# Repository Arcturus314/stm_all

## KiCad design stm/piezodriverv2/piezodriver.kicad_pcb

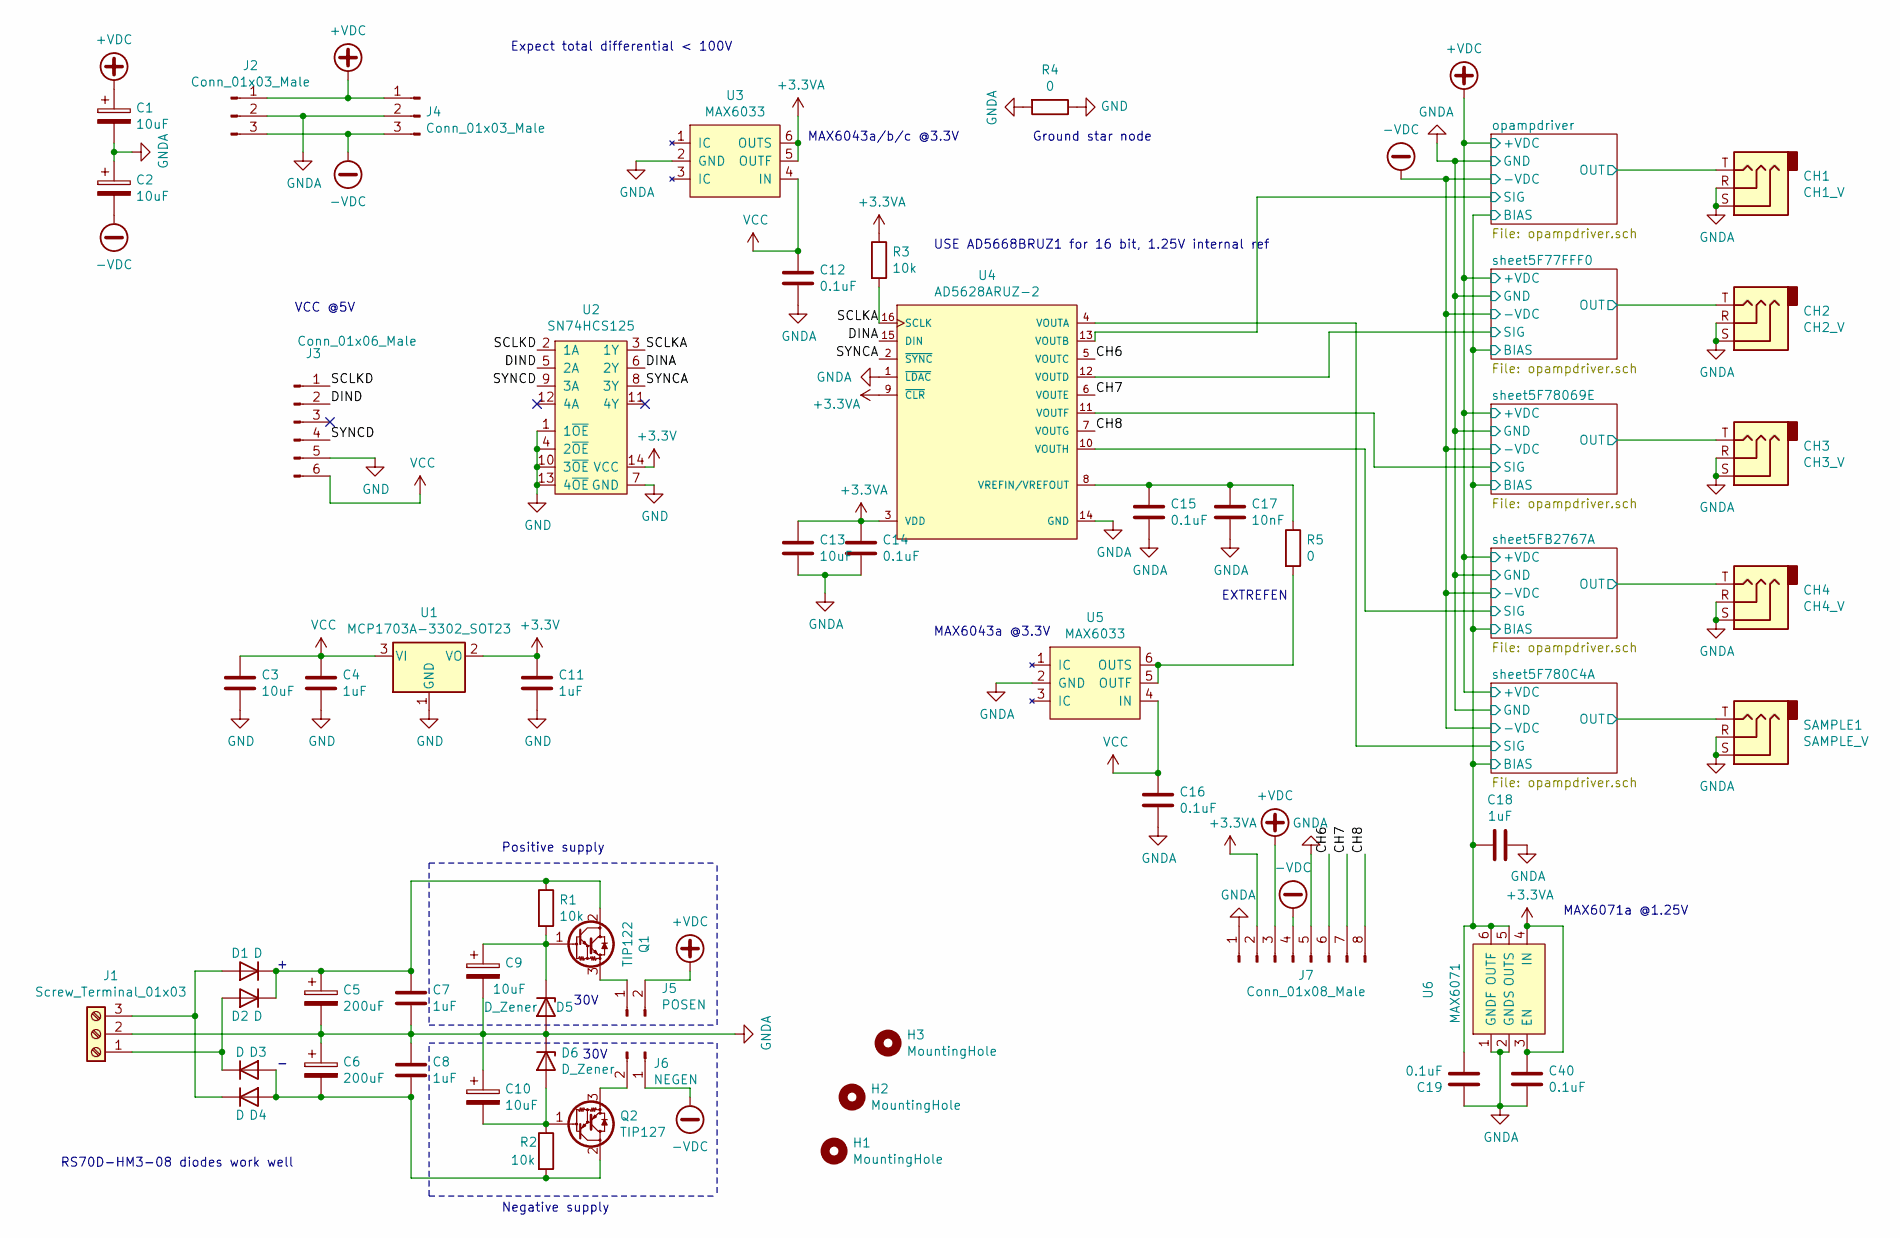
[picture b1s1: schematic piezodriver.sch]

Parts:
C1, C2, C9, C10: 10uF; CP_Radial_D5.0mm_P2.50mm
C3, C13: 10uF; C_0805_2012Metric_Pad1.18x1.45mm_HandSolder
C4, C7, C8, C11, C18: 1uF; C_0805_2012Metric_Pad1.18x1.45mm_HandSolder
C5, C6: 200uF; CP_Radial_D12.5mm_P5.00mm
C12, C14, C15, C16, C19, C40: 0.1uF; C_0805_2012Metric_Pad1.18x1.45mm_HandSolder
C17: 10nF; C_0805_2012Metric_Pad1.18x1.45mm_HandSolder
CH1: CH1_V; Jack_3.5mm_CUI_SJ-3523-SMT_Horizontal
CH2: CH2_V; Jack_3.5mm_CUI_SJ-3523-SMT_Horizontal
CH3: CH3_V; Jack_3.5mm_CUI_SJ-3523-SMT_Horizontal
CH4: CH4_V; Jack_3.5mm_CUI_SJ-3523-SMT_Horizontal
D1, D2, D3, D4: D; D_SMF
D5, D6: D_Zener; D_SOD-323_HandSoldering
H1, H2, H3: MountingHole; MountingHole_3.2mm_M3
J1: Screw_Terminal_01x03; TerminalBlock_Phoenix_MKDS-1,5-3-5.08_1x03_P5.08mm_Horizont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
J2, J4: Conn_01x03_Male; PinHeader_1x03_P2.54mm_Vertical
J3: Conn_01x06_Male; PinHeader_1x06_P2.54mm_Vertical
J5: POSEN; PinHeader_1x02_P2.54mm_Vertical
J6: NEGEN; PinHeader_1x02_P2.54mm_Vertical
J7: Conn_01x08_Male; PinHeader_1x08_P2.54mm_Vertical
Q1: TIP122; TO-220-3_Vertical
Q2: TIP127; TO-220-3_Vertical
R1, R2, R3: 10k; R_0805_2012Metric_Pad1.20x1.40mm_HandSolder
R4, R5: 0; R_0805_2012Metric_Pad1.20x1.40mm_HandSolder
SAMPLE1: SAMPLE_V; Jack_3.5mm_CUI_SJ-3523-SMT_Horizontal
U1: MCP1703A-3302_SOT23; SOT-23
U2: SN74HCS125; TSSOP-14_4.4x5mm_P0.65mm
U3, U5: MAX6033; SOT-23-6_Handsoldering
U4: AD5628ARUZ-2; TSSOP-16_4.4x5mm_P0.65mm
U6: MAX6071; SOT-23-6_Handsoldering

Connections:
+3.3VA: C13.1, C14.1, C40.1, J7.2, R3.1, U3.5 (OUTF), U3.6 (OUTS), U4.3 (VDD), U4.9 (~CLR~), U6.3 (EN), U6.4 (IN)
+3V3: C11.1, U1.2 (VO), U2.14 (VCC)
+VDC: C1.1, J2.1, J4.1, J5.2, J7.3; also elsewhere on the board
-VDC: C2.2, J2.3, J4.3, J6.1, J7.4; also elsewhere on the board
/CH6: J7.6, U4.5 (VOUTC)
/CH7: J7.7, U4.6 (VOUTE)
/CH8: J7.8, U4.7 (VOUTG)
/DINA: U2.6 (2Y), U4.15 (DIN)
/DIND: J3.2, U2.5 (2A)
/SCLKA: R3.2, U2.3 (1Y), U4.16 (SCLK)
/SCLKD: J3.1, U2.2 (1A)
/SYNCA: U2.8 (3Y), U4.2 (~SYNC~)
/SYNCD: J3.4, U2.9 (3A)
/opampdriver/BIAS: C18.1, C19.2, U6.5 (OUTS), U6.6 (OUTF); also elsewhere on the board
/opampdriver/OUT: CH1.T; also elsewhere on the board
/opampdriver/SIG: U4.13 (VOUTB); also elsewhere on the board
/sheet5F77FFF0/OUT: CH2.T; also elsewhere on the board
/sheet5F77FFF0/SIG: U4.12 (VOUTD); also elsewhere on the board
/sheet5F780C4A/OUT: SAMPLE1.T; also elsewhere on the board
/sheet5F780C4A/SIG: U4.4 (VOUTA); also elsewhere on the board
/sheet5F78069E/OUT: CH3.T; also elsewhere on the board
/sheet5F78069E/SIG: U4.11 (VOUTF); also elsewhere on the board
/sheet5FB2767A/OUT: CH4.T; also elsewhere on the board
/sheet5FB2767A/SIG: U4.10 (VOUTH); also elsewhere on the board
GND: C3.2, C4.2, C11.2, J3.5, R4.1, U1.1 (GND), U2.1 (1~OE), U2.4 (2~OE), U2.7 (GND), U2.10 (3~OE), U2.13 (4~OE)
GNDA: C1.2, C2.1, C5.2, C6.1, C7.2, C8.1, C9.2, C10.1, C12.2, C13.2, C14.2, C15.2, C16.2, C17.2, C18.2, C19.1, C40.2, CH1.R, CH1.S, CH2.R, CH2.S, CH3.R, CH3.S, CH4.R, CH4.S, D5.2 (A), D6.1 (K), J1.2, J2.2, J4.2, J7.1, J7.5, R4.2, SAMPLE1.R, SAMPLE1.S, U3.2 (GND), U4.1 (~LDAC~), U4.14 (GND), U5.2 (GND), U6.1 (GNDF), U6.2 (GNDS); also elsewhere on the board
unnamed: C5.1, C7.1, D1.1 (K), D2.1 (K), Q1.2 (C), R1.1
unnamed: C6.2, C8.2, D3.2 (A), D4.2 (A), Q2.2 (C), R2.2
unnamed: C9.1, D5.1 (K), Q1.1 (B), R1.2
unnamed: C10.2, D6.2 (A), Q2.1 (B), R2.1
unnamed: C15.1, C17.1, R5.1, U4.8 (VREFIN/VREFOUT)
unnamed: D1.2 (A), D4.1 (K), J1.3
unnamed: D2.2 (A), D3.1 (K), J1.1
unnamed: J5.1, Q1.3 (E)
unnamed: J6.2, Q2.3 (E)
unnamed: R5.2, U5.5 (OUTF), U5.6 (OUTS)
VCC: C3.1, C4.1, C12.1, C16.1, J3.6, U1.3 (VI), U3.4 (IN), U5.4 (IN)

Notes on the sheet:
Expect total differential < 100V
USE AD5668BRUZ1 for 16 bit, 1.25V internal ref
EXTREFEN
MAX6043a @3.3V
MAX6071a @1.25V
VCC @5V
Ground star node
MAX6043a/b/c @3.3V
RS70D-HM3-08 diodes work well
Negative supply
30V
Positive supply

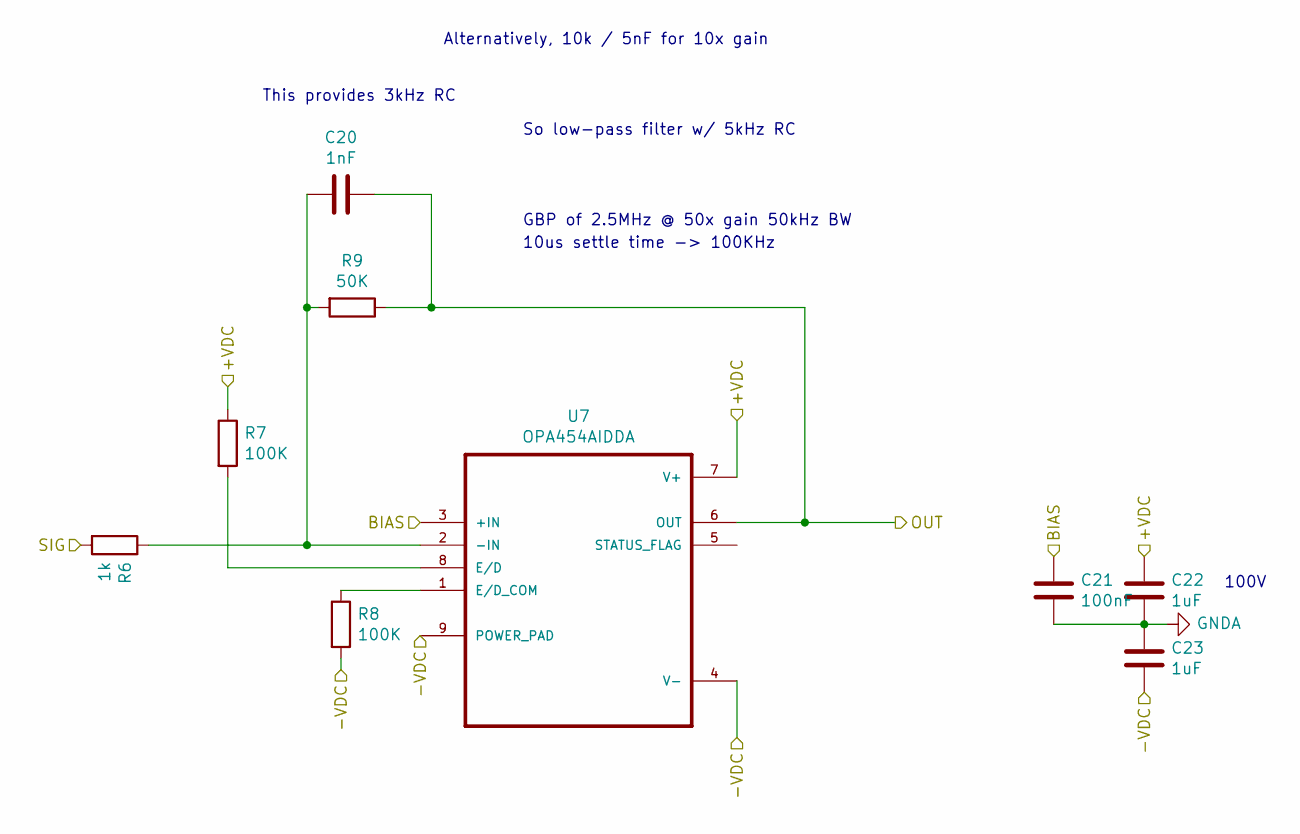
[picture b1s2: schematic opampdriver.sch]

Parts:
C20: 1nF; C_0805_2012Metric_Pad1.18x1.45mm_HandSolder
C21: 100nF; C_0805_2012Metric_Pad1.18x1.45mm_HandSolder
C22, C23: 1uF; C_0805_2012Metric_Pad1.18x1.45mm_HandSolder
R6: 1k; R_0805_2012Metric_Pad1.20x1.40mm_HandSolder
R7, R8: 100K; R_0805_2012Metric_Pad1.20x1.40mm_HandSolder
R9: 50K; R_0805_2012Metric_Pad1.20x1.40mm_HandSolder
U7: OPA454AIDDA; NOPB

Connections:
+VDC: C22.1, R7.1, U7.7 (V+); also elsewhere on the board
-VDC: C23.2, R8.2, U7.4 (V-), U7.9 (POWER_PAD); also elsewhere on the board
/opampdriver/BIAS: C21.1, U7.3 (+IN); also elsewhere on the board
/opampdriver/OUT: C20.1, R9.1, U7.6 (OUT); also elsewhere on the board
/opampdriver/SIG: R6.2; also elsewhere on the board
GNDA: C21.2, C22.2, C23.1; also elsewhere on the board
unnamed: C20.2, R6.1, R9.2, U7.2 (-IN)
unnamed: R7.2, U7.8 (E/D)
unnamed: R8.1, U7.1 (E/D_COM)

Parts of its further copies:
C24, C28, C32, C36: 1nF; C_0805_2012Metric_Pad1.18x1.45mm_HandSolder
C25, C29, C33, C37: 100nF; C_0805_2012Metric_Pad1.18x1.45mm_HandSolder
C26, C27, C30, C31, C34, C35, C38, C39: 1uF; C_0805_2012Metric_Pad1.18x1.45mm_HandSolder
R10, R14, R18, R22: 1k; R_0805_2012Metric_Pad1.20x1.40mm_HandSolder
R11, R12, R15, R16, R19, R20, R23, R24: 100K; R_0805_2012Metric_Pad1.20x1.40mm_HandSolder
R13, R17, R21, R25: 50K; R_0805_2012Metric_Pad1.20x1.40mm_HandSolder
U8, U9, U10, U11: OPA454AIDDA; NOPB

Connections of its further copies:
+VDC: C26.1, C30.1, C34.1, C38.1, R11.1, R15.1, R19.1, R23.1, U8.7 (V+), U9.7 (V+), U10.7 (V+), U11.7 (V+); also elsewhere on the board
-VDC: C27.2, C31.2, C35.2, C39.2, R12.2, R16.2, R20.2, R24.2, U8.4 (V-), U8.9 (POWER_PAD), U9.4 (V-), U9.9 (POWER_PAD), U10.4 (V-), U10.9 (POWER_PAD), U11.4 (V-), U11.9 (POWER_PAD); also elsewhere on the board
/opampdriver/BIAS: C25.1, C29.1, C33.1, C37.1, U8.3 (+IN), U9.3 (+IN), U10.3 (+IN), U11.3 (+IN); also elsewhere on the board
/sheet5F77FFF0/OUT: C24.1, R13.1, U8.6 (OUT); also elsewhere on the board
/sheet5F77FFF0/SIG: R10.2; also elsewhere on the board
/sheet5F780C4A/OUT: C32.1, R21.1, U10.6 (OUT); also elsewhere on the board
/sheet5F780C4A/SIG: R18.2; also elsewhere on the board
/sheet5F78069E/OUT: C28.1, R17.1, U9.6 (OUT); also elsewhere on the board
/sheet5F78069E/SIG: R14.2; also elsewhere on the board
/sheet5FB2767A/OUT: C36.1, R25.1, U11.6 (OUT); also elsewhere on the board
/sheet5FB2767A/SIG: R22.2; also elsewhere on the board
GNDA: C25.2, C26.2, C27.1, C29.2, C30.2, C31.1, C33.2, C34.2, C35.1, C37.2, C38.2, C39.1; also elsewhere on the board
unnamed: C24.2, R10.1, R13.2, U8.2 (-IN)
unnamed: C28.2, R14.1, R17.2, U9.2 (-IN)
unnamed: C32.2, R18.1, R21.2, U10.2 (-IN)
unnamed: C36.2, R22.1, R25.2, U11.2 (-IN)
unnamed: R11.2, U8.8 (E/D)
unnamed: R12.1, U8.1 (E/D_COM)
unnamed: R15.2, U9.8 (E/D)
unnamed: R16.1, U9.1 (E/D_COM)
unnamed: R19.2, U10.8 (E/D)
unnamed: R20.1, U10.1 (E/D_COM)
unnamed: R23.2, U11.8 (E/D)
unnamed: R24.1, U11.1 (E/D_COM)

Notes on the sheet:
GBP of 2.5MHz @ 50x gain 50kHz BW
10us settle time -> 100KHz
So low-pass filter w/ 5kHz RC
This provides 3kHz RC
Alternatively, 10k / 5nF for 10x gain
100V

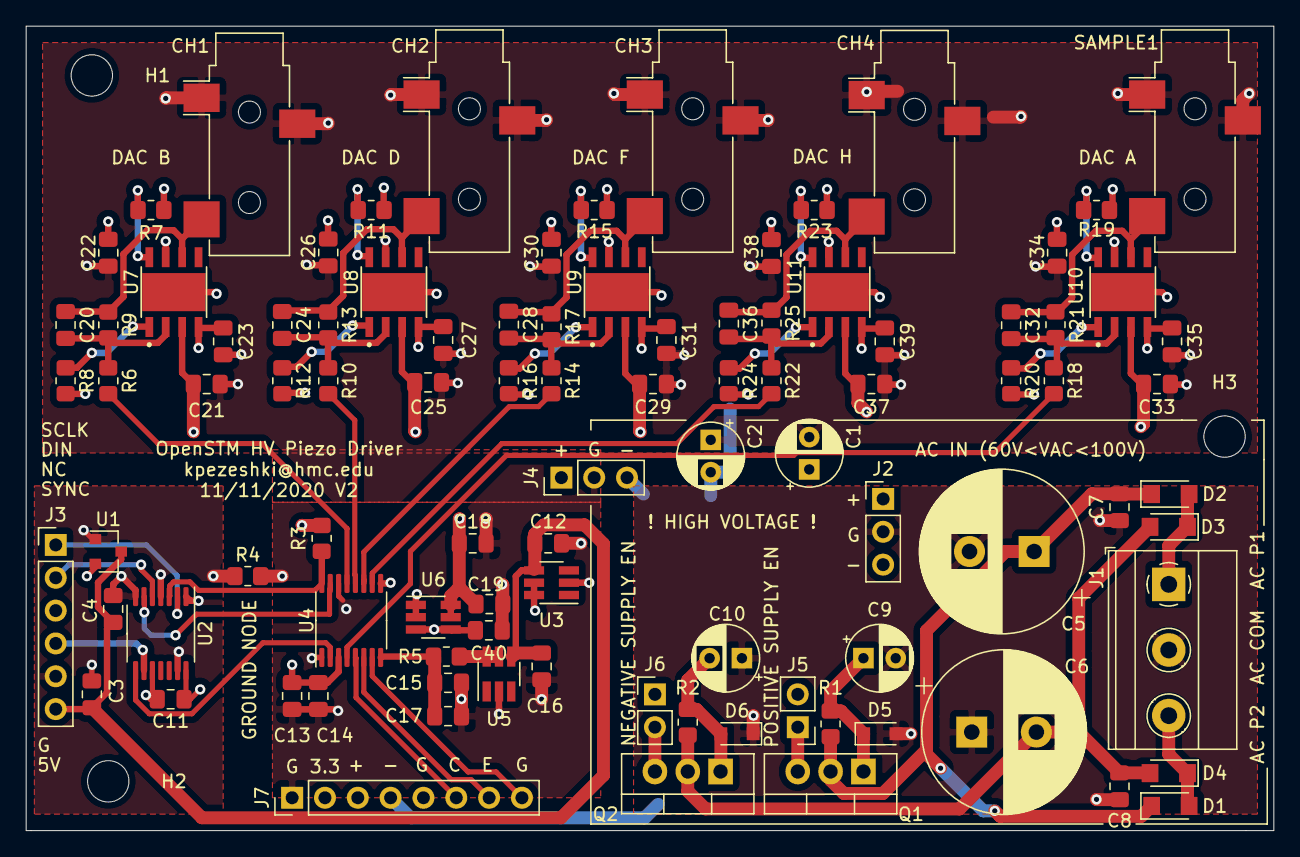
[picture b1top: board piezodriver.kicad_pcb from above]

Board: 4 copper layers, 96.5 x 62.2 mm, 99 parts (0 on the bottom side), 52 nets.

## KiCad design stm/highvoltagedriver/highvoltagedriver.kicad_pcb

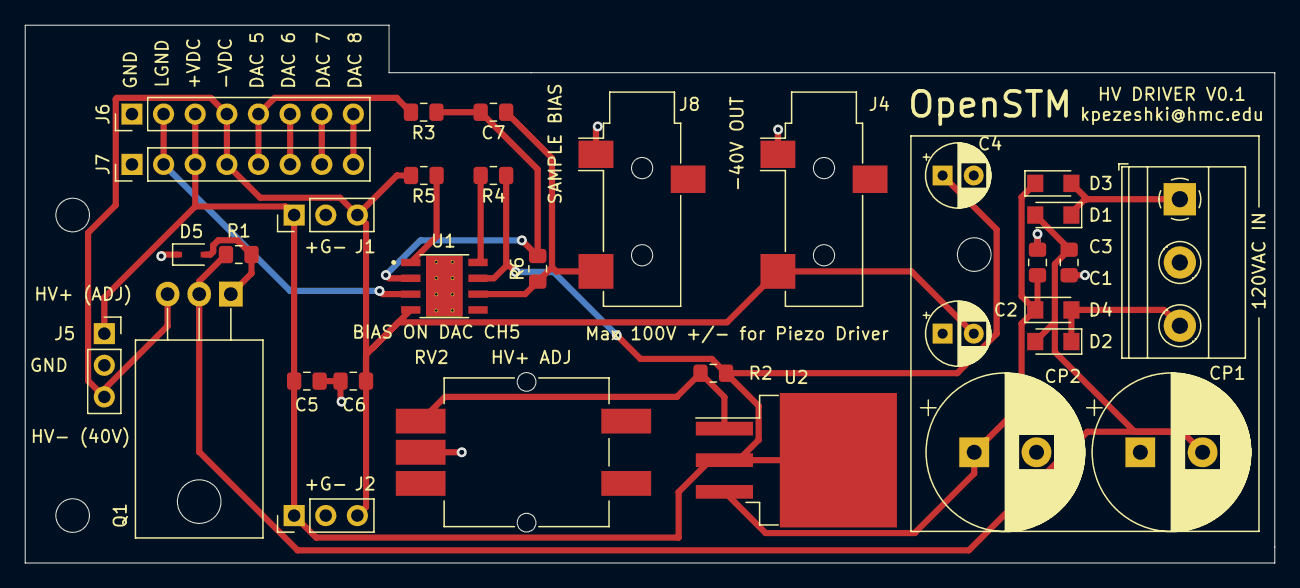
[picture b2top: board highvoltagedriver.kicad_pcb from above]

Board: 2 copper layers, 100.3 x 43.2 mm, 32 parts (0 on the bottom side), 18 nets.

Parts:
C1, C3, C5, C6: 1uF; C_0805_2012Metric_Pad1.15x1.40mm_HandSolder
C2, C4: 10uF; CP_Radial_D5.0mm_P2.50mm
C7: 1nF; C_0805_2012Metric_Pad1.15x1.40mm_HandSolder
CP1, CP2: 200uF; CP_Radial_D12.5mm_P5.00mm
D1, D2, D3, D4: D; D_SMF
D5: D_Zener; D_SOD-323
J1, J2: Conn_01x03_Male; PinHeader_1x03_P2.54mm_Vertical
J3: Screw_Terminal_01x03; TerminalBlock_Phoenix_MKDS-1,5-3-5.08_1x03_P5.08mm_Horizont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
J4, J8: AudioJack2; Jack_3.5mm_CUI_SJ-3523-SMT_Horizontal
J5: Conn_01x03_Female; PinSocket_1x03_P2.54mm_Vertical
J6: Conn_01x08_Male; PinHeader_1x08_P2.54mm_Vertical
J7: Conn_01x08_Female; PinHeader_1x08_P2.54mm_Vertical
Q1: TIP127; TO-220-3_Horizontal_TabDown
R1: 10k; R_0805_2012Metric_Pad1.15x1.40mm_HandSolder
R2: 100; R_0805_2012Metric_Pad1.15x1.40mm_HandSolder
R3: 1k; R_0805_2012Metric_Pad1.15x1.40mm_HandSolder
R4, R5: 100K; R_0805_2012Metric_Pad1.15x1.40mm_HandSolder
R6: 50K; R_0805_2012Metric_Pad1.15x1.40mm_HandSolder
RV2: 10k; Potentiometer_Bourns_PRS11S_Vertical
U1: OPA454AIDDA; NOPB
U2: TL783; TO-263-3_TabPin2

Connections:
/DACBIAS: J6.5, J7.5, R3.2
/HVN: C2.2, C6.1, J1.3, J2.3, J4.T, J5.3, J6.4, J7.4, Q1.3, R5.2, U1.4
/HVP: C4.1, C5.1, J1.1, J2.1, J5.1, J6.3, J7.3, R2.2, R4.1, U1.7, U2.2
/biasamp/BIAS: J6.2, J7.2, U1.3
/biasamp/OUT: C7.1, J8.T, R6.1, U1.6
/hvpower/negreg/VNEG: C1.2, CP1.2, D1.2, D2.2, Q1.2, R1.2
GND: C1.1, C2.1, C3.2, C4.2, C5.2, C6.2, CP1.1, CP2.2, D5.1, J1.2, J2.2, J3.2, J4.S, J5.2, J6.1, J7.1, J8.S, RV2.2
unnamed: C3.1, CP2.1, D3.1, D4.1, U2.3
unnamed: C7.2, R3.1, R6.2, U1.2
unnamed: D1.1, D3.2, J3.1
unnamed: D2.1, D4.2, J3.3
unnamed: D5.2, Q1.1, R1.1
unnamed: J6.6, J7.6
unnamed: J6.7, J7.7
unnamed: J6.8, J7.8
unnamed: R2.1, RV2.1, U2.1
unnamed: R4.2, U1.8
unnamed: R5.1, U1.1

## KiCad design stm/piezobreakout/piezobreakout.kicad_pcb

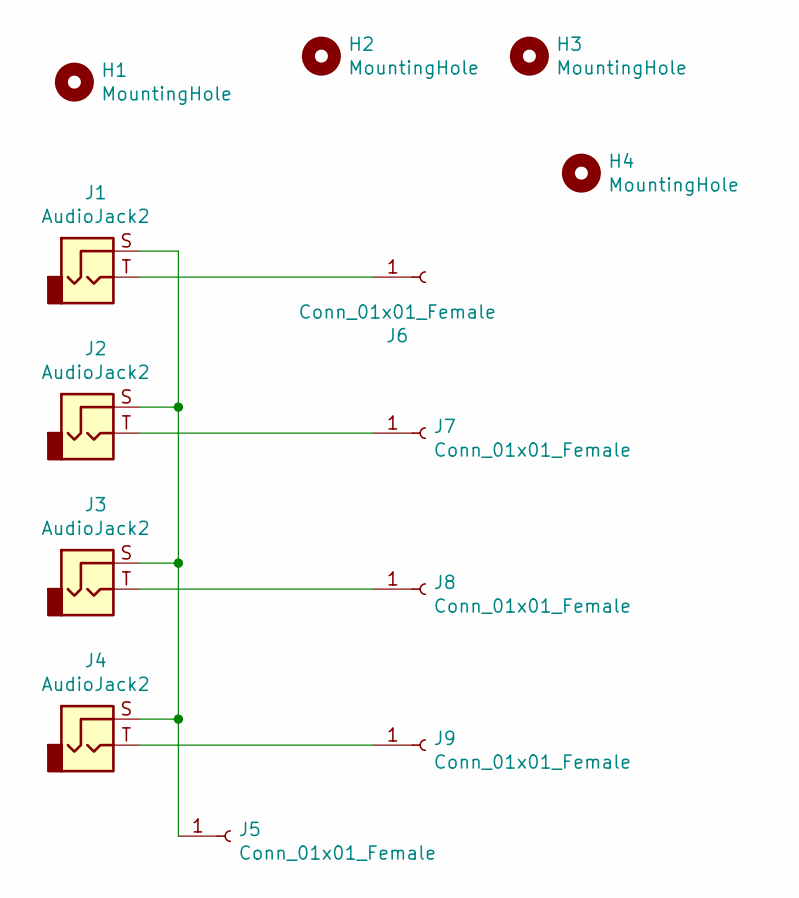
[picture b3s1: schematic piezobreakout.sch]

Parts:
H1, H2, H3, H4: MountingHole; MountingHole_3.2mm_M3
J1, J2, J3, J4: AudioJack2; Jack_3.5mm_CUI_SJ-3523-SMT_Horizontal
J5, J6, J7, J8, J9: Conn_01x01_Female; PinHeader_1x01_P2.54mm_Vertical

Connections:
unnamed: J1.S, J2.S, J3.S, J4.S, J5.1
unnamed: J1.T, J6.1
unnamed: J2.T, J7.1
unnamed: J3.T, J8.1
unnamed: J4.T, J9.1

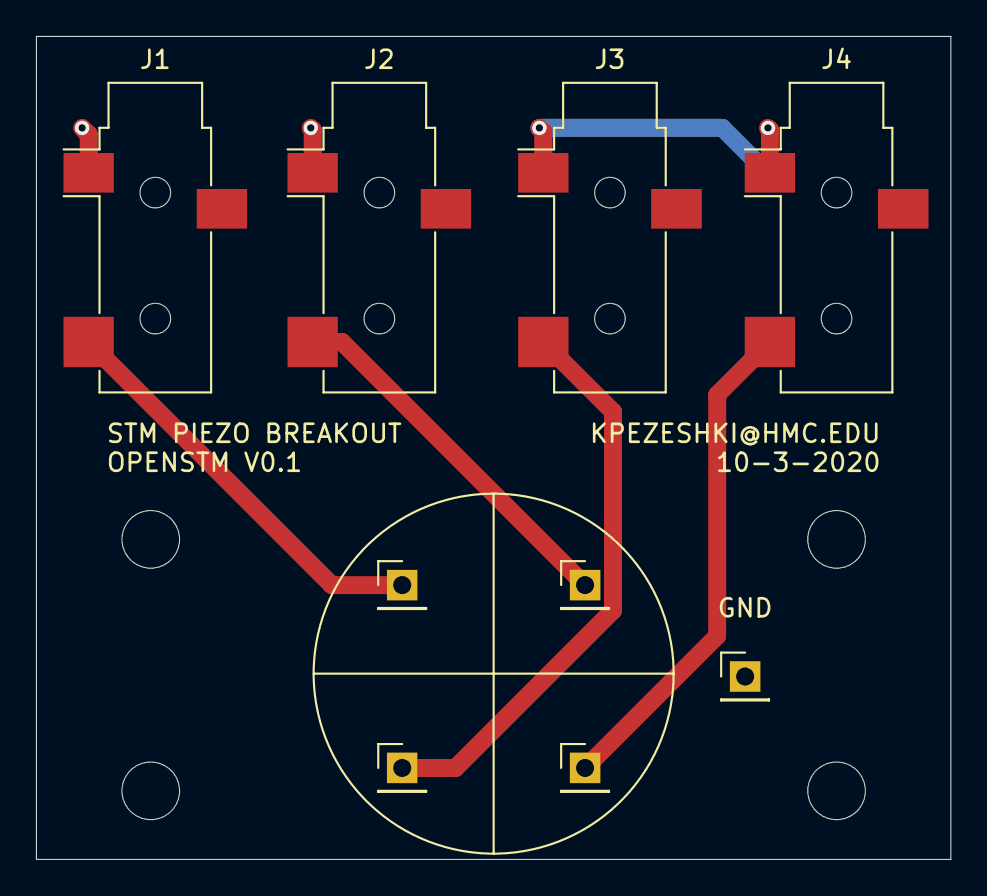
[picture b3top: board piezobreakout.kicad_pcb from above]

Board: 2 copper layers, 50.8 x 45.7 mm, 13 parts (0 on the bottom side), 5 nets.

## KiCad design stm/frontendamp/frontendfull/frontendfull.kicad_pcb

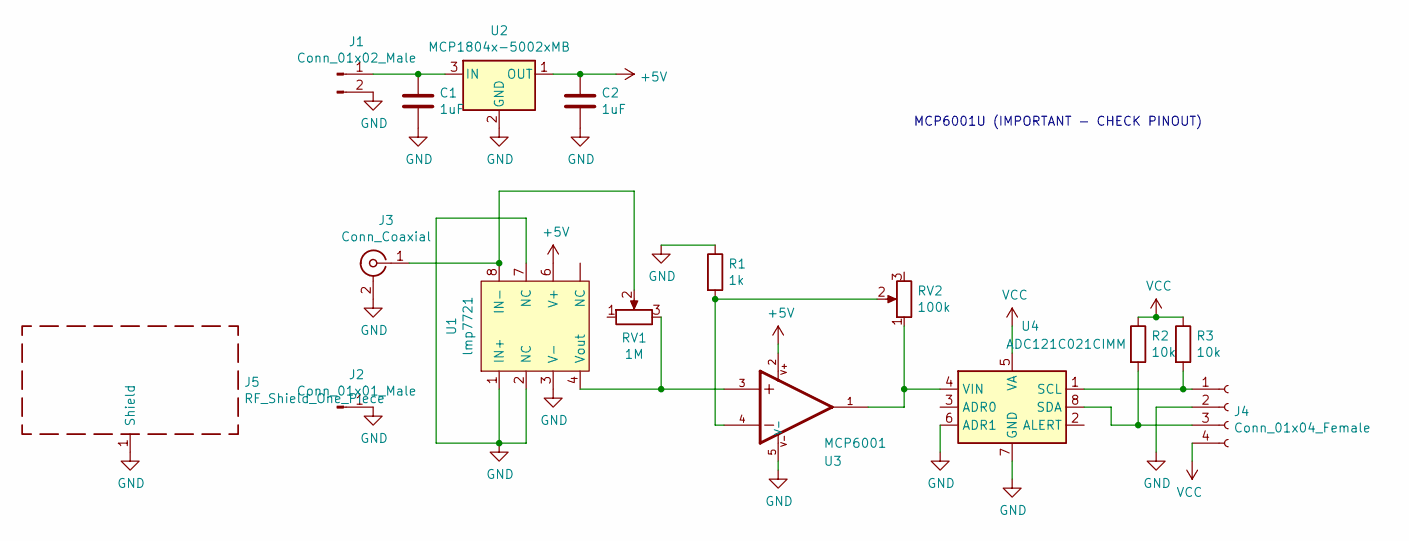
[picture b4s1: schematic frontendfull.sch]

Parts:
C1, C2: 1uF; C_0805_2012Metric_Pad1.15x1.40mm_HandSolder
J1: Conn_01x02_Male; PinSocket_1x02_P2.54mm_Vertical
J2: Conn_01x01_Male; PinSocket_1x01_P2.54mm_Vertical
J3: Conn_Coaxial; U.FL_Hirose_U.FL-R-SMT-1_Vertical
J4: Conn_01x04_Female; PinHeader_1x04_P2.54mm_Vertical
J5: RF_Shield_One_Piece; Laird_Technologies_BMI-S-202-F_16.50x16.50mm
R1: 1k; R_0805_2012Metric_Pad1.15x1.40mm_HandSolder
R2, R3: 10k; R_0805_2012Metric_Pad1.15x1.40mm_HandSolder
RV1: 1M; Potentiometer_Bourns_3314J_Vertical
RV2: 100k; Potentiometer_Bourns_3314J_Vertical
U1: lmp7721
U2: MCP1804x-5002xMB; SOT-89-3
U3: MCP6001; SOT-23-5_HandSoldering
U4: ADC121C021CIMM; MSOP-8_3x3mm_P0.65mm

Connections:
+5V: C2.1, U1.6 (V+), U2.1 (OUT), U3.2
GND: C1.2, C2.2, J1.2, J2.1, J3.2 (Ext), J4.2, J5.1, R1.1, U1.1 (IN+), U1.2 (NC), U1.3 (V-), U1.7 (NC), U2.2 (GND), U3.5 (V-), U4.6 (ADR1), U4.7 (GND)
unnamed: C1.1, J1.1, U2.3 (IN)
unnamed: J3.1 (In), RV1.2, U1.8 (IN-)
unnamed: J4.1, R3.2, U4.1 (SCL)
unnamed: J4.3, R2.2, U4.8 (SDA)
unnamed: R1.2, RV2.2, U3.4
unnamed: RV1.3, U1.4 (Vout), U3.3
unnamed: RV2.1, U3.1, U4.4 (VIN)
VCC: J4.4, R2.1, R3.1, U4.5 (VA)

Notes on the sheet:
MCP6001U (IMPORTANT - CHECK PINOUT)

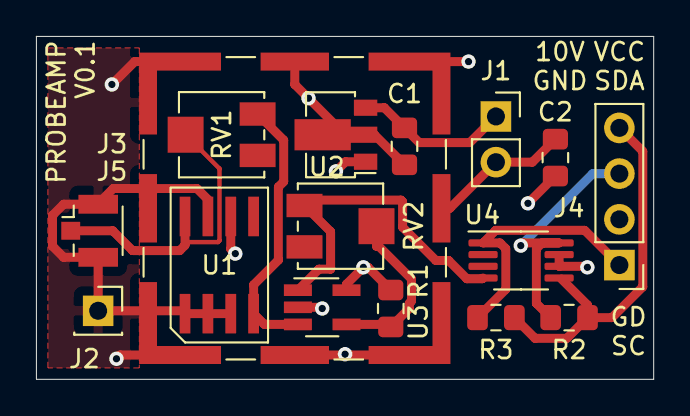
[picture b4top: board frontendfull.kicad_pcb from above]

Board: 4 copper layers, 34.3 x 19.0 mm, 16 parts (0 on the bottom side), 10 nets.

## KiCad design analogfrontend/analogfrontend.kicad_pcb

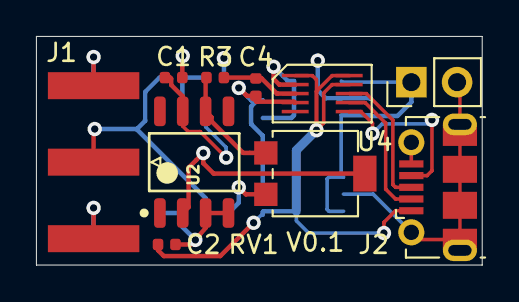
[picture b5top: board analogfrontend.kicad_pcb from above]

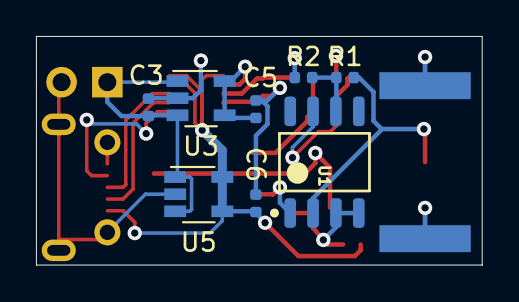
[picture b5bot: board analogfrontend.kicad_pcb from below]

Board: 4 copper layers, 24.8 x 12.7 mm, 18 parts (8 on the bottom side), 12 nets.

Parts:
C1, C2: 100nF; C_0402_1005Metric
C3: 4.7uF; C_0402_1005Metric
C4: 2nF; C_0402_1005Metric
C5, C6: 2.2uF; C_0402_1005Metric
J1: Conn_Coaxial; SMA_Amphenol_132289_EdgeMount
J2: USB_OTG; USB_Micro-B_Molex-105017-0001
J3: Conn_01x02_Male; PinHeader_1x02_P2.54mm_Vertical
R1: 1M; R_0402_1005Metric
R2: 100; R_0402_1005Metric
R3: 22; R_0402_1005Metric
RV1: 10k; Potentiometer_Bourns_3314G_Vertical
U1, U2: OPA124UA; Texas_Instruments-OPA124UA-Level_A
U3: ADP7142AUJZ-1.8; TSOT-23-5
U4: MCP33131
U5: ADP7142AUJZ-3.3; TSOT-23-5

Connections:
+1V8: C5.1, U3.4, U3.5, U4.2
+3V3: C1.1, C2.1, C6.1, J2.1, U1.7, U2.7, U4.1, U4.9, U4.10, U5.4, U5.5
+5V: C3.1, J3.1, U3.1, U3.3, U5.1, U5.3
GND: C1.2, C2.2, C3.2, C4.2, C5.2, C6.2, J1.2, J2.5, J2.6, J3.2, U1.3, U1.4, U2.3, U2.4, U3.2, U4.4, U5.2
unnamed: C4.1, R3.1, U4.3
unnamed: J1.1, R1.2, U1.2
unnamed: J2.2, U4.7
unnamed: J2.3, U4.8
unnamed: J2.4, U4.6
unnamed: R1.1, R2.2, U1.6
unnamed: R2.1, RV1.2, U2.2
unnamed: R3.2, RV1.1, U2.6

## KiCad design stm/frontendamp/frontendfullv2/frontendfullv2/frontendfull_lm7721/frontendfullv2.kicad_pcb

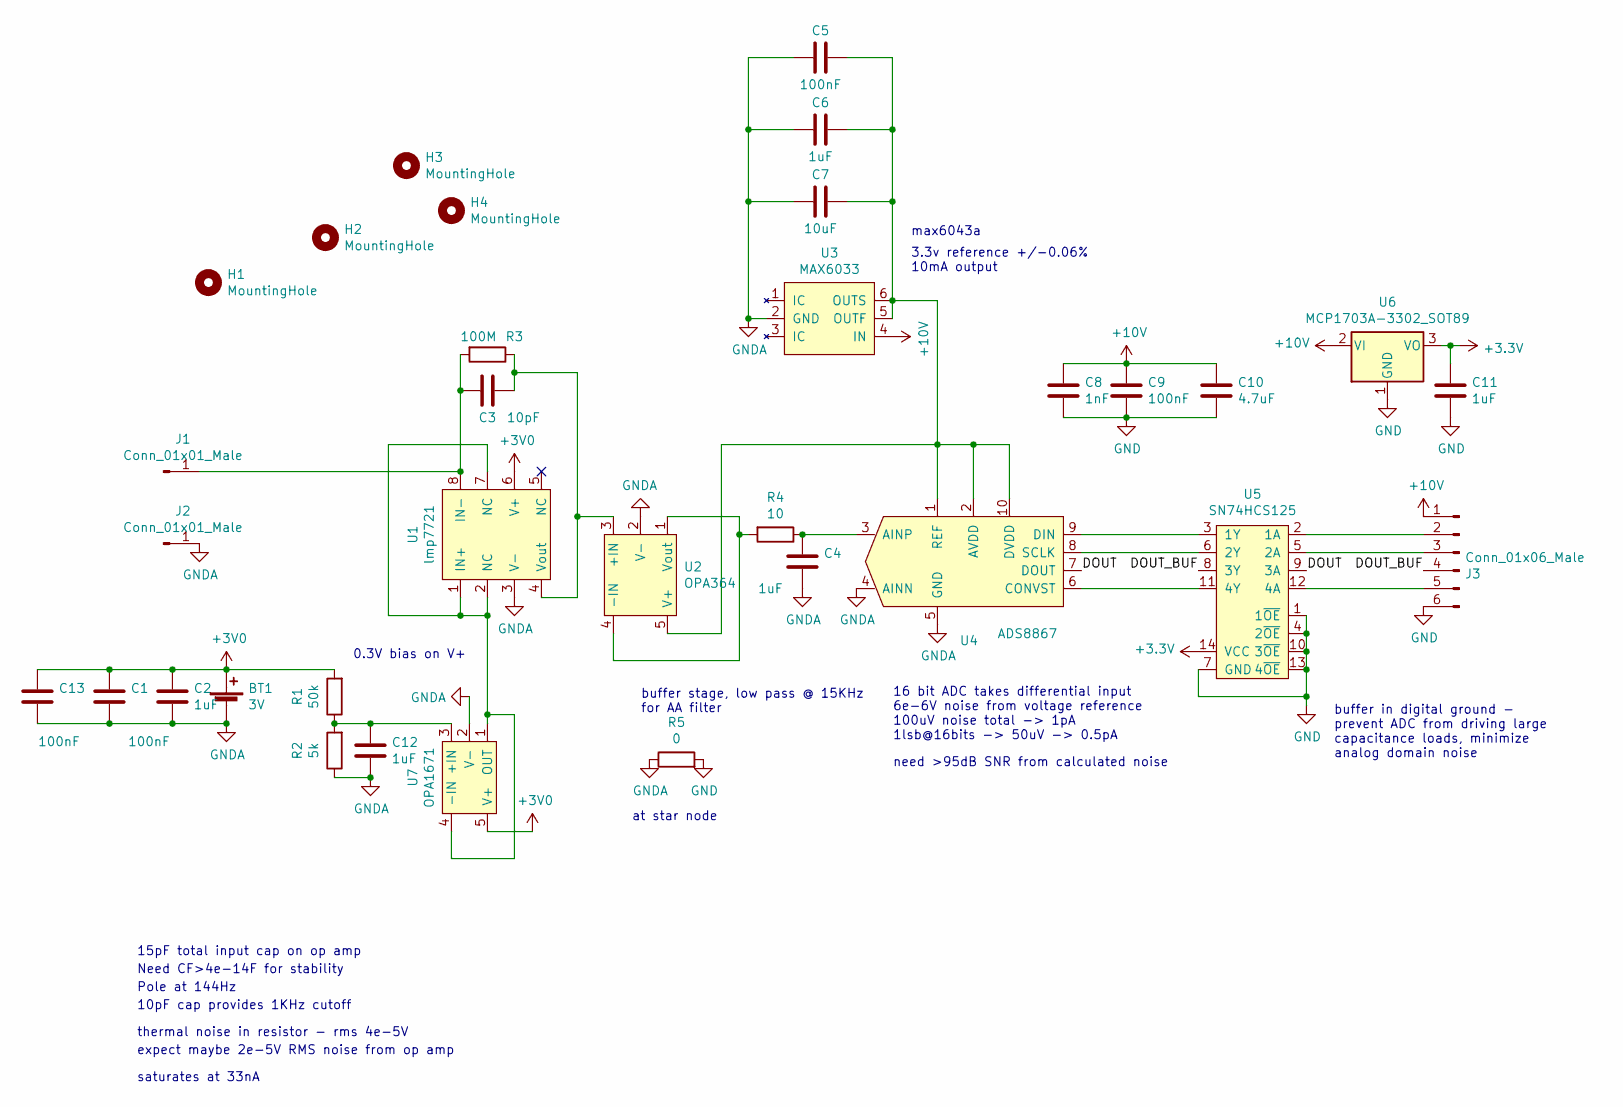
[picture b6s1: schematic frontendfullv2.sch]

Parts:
BT1: 3V; BatteryHolder_Keystone_1058_1x2032
C1, C5, C9: 100nF; C_0603_1608Metric_Pad1.08x0.95mm_HandSolder
C2, C4, C6, C11: 1uF; C_0603_1608Metric_Pad1.08x0.95mm_HandSolder
C3: 10pF; C_0805_2012Metric_Pad1.15x1.40mm_HandSolder
C7: 10uF; C_0805_2012Metric_Pad1.15x1.40mm_HandSolder
C8: 1nF; C_0603_1608Metric_Pad1.08x0.95mm_HandSolder
C10: 4.7uF; C_0603_1608Metric_Pad1.08x0.95mm_HandSolder
C12: 1uF; C_0603_1608Metric_Pad1.05x0.95mm_HandSolder
C13: 100nF; C_0603_1608Metric_Pad1.05x0.95mm_HandSolder
H1, H2, H3, H4: MountingHole; MountingHole_2.2mm_M2
J1: Conn_01x01_Male; smallpad
J2: Conn_01x01_Male; PinHeader_1x01_P2.54mm_Vertical
J3: Conn_01x06_Male; PinSocket_1x06_P2.54mm_Vertical
R1: 50k; R_0603_1608Metric_Pad0.98x0.95mm_HandSolder
R2: 5k; R_0603_1608Metric_Pad0.98x0.95mm_HandSolder
R3: 100M; R_0805_2012Metric
R4: 10; R_0603_1608Metric_Pad0.98x0.95mm_HandSolder
R5: 0; R_0603_1608Metric_Pad0.98x0.95mm_HandSolder
U1: lmp7721
U2: OPA364; SOT-23-5_HandSoldering
U3: MAX6033; SOT-23-6_Handsoldering
U4: ADS8867; VSSOP-10_3x3mm_P0.5mm
U5: SN74HCS125; TSSOP-14_4.4x5mm_P0.65mm
U6: MCP1703A-3302_SOT89; SOT-89-3
U7: OPA1671; SOT-23-5_HandSoldering

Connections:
+3V0: BT1.1 (+), C1.1, C2.1, C13.1, R1.2, U1.6 (V+), U7.5 (V+)
+3V3: C11.1, U5.14 (VCC), U6.3 (VO)
+10V: C8.1, C9.1, C10.1, J3.1, U3.4 (IN), U6.2 (VI)
/DOUT: U4.7 (DOUT), U5.9 (3A)
/DOUT_BUF: J3.4, U5.8 (3Y)
GND: C8.2, C9.2, C10.2, C11.2, J3.6, R5.2, U5.1 (1~OE), U5.4 (2~OE), U5.7 (GND), U5.10 (3~OE), U5.13 (4~OE), U6.1 (GND)
GNDA: BT1.2 (-), C1.2, C2.2, C4.2, C5.2, C6.2, C7.2, C12.2, C13.2, J2.1, R2.1, R5.1, U1.3 (V-), U2.2 (V-), U3.2 (GND), U4.4 (AINN), U4.5 (GND), U7.2 (V-)
unnamed: C3.1, J1.1, R3.2, U1.8 (IN-)
unnamed: C3.2, R3.1, U1.4 (Vout), U2.3 (+IN)
unnamed: C4.1, R4.1, U4.3 (AINP)
unnamed: C5.1, C6.1, C7.1, U2.5 (V+), U3.5 (OUTF), U3.6 (OUTS), U4.1 (REF), U4.2 (AVDD), U4.10 (DVDD)
unnamed: C12.1, R1.1, R2.2, U7.3 (+IN)
unnamed: J3.2, U5.2 (1A)
unnamed: J3.3, U5.5 (2A)
unnamed: J3.5, U5.12 (4A)
unnamed: R4.2, U2.1 (Vout), U2.4 (-IN)
unnamed: U1.1 (IN+), U1.2 (NC), U1.7 (NC), U7.1 (OUT), U7.4 (-IN)
unnamed: U4.6 (CONVST), U5.11 (4Y)
unnamed: U4.8 (SCLK), U5.6 (2Y)
unnamed: U4.9 (DIN), U5.3 (1Y)

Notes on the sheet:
16 bit ADC takes differential input 6e-6V noise from voltage reference 100uV noise total -> 1pA 1lsb@16bits -> 50uV -> 0.5pA
max6043a
3.3v reference +/-0.06% 10mA output
0.3V bias on V+
thermal noise in resistor - rms 4e-5V
10pF cap provides 1KHz cutoff
Pole at 144Hz
Need CF>4e-14F for stability
15pF total input cap on op amp
buffer stage, low pass @ 15KHz for AA filter
expect maybe 2e-5V RMS noise from op amp
need >95dB SNR from calculated noise
buffer in digital ground - prevent ADC from driving large capacitance loads, minimize analog domain noise
at star node
saturates at 33nA

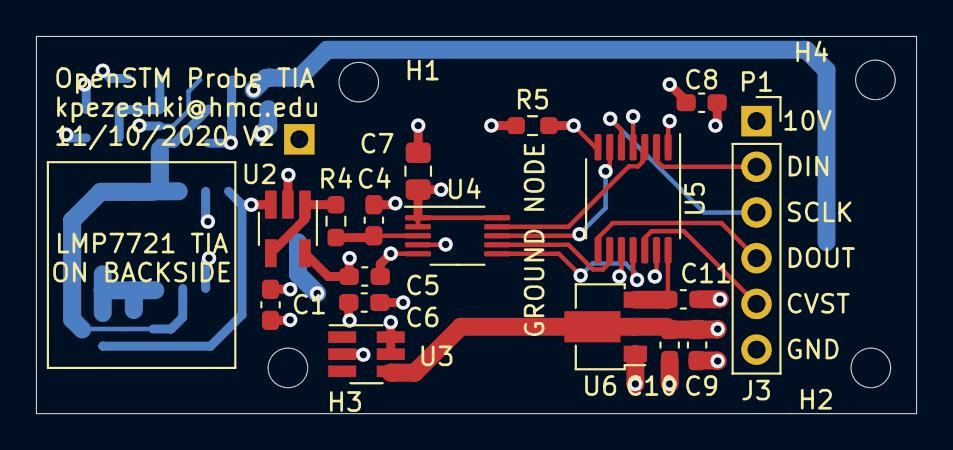
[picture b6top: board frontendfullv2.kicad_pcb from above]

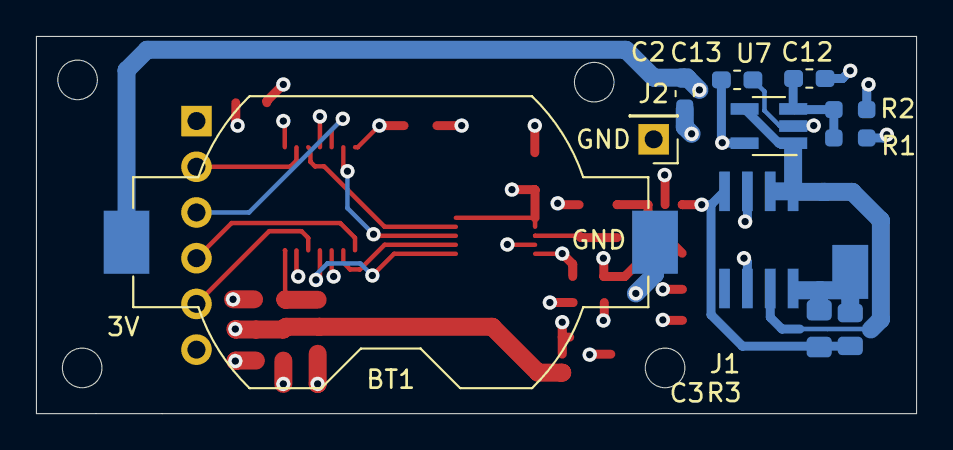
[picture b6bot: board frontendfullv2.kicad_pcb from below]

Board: 4 copper layers, 48.9 x 21.0 mm, 33 parts (12 on the bottom side), 20 nets.
